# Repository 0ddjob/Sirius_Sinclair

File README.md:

# Сириус (Sirius) Sinclair ZX Spectrum Clone
## Introduction
I have two examples of this machine - they have the same case & keyboard but the motherboard is different.  I'm mainly interested in the smaller board as this seems to be the smallest implementation of a ZX Spectrum I've come across.

This machine was initially a bit of a mystery - well, obviously it's a Sinclair ZX Spectrum clone.  It has all Soviet-era parts (dated mostly 1991 & 1992) including a beautiful, ceramic Т34ВМ1 CPU, a Т34РЕ1-020 ROM (containing the Czechoslovak "Didaktik Skalica" firmware) and absolutely no manufacture markings on the case or motherboard.

Thanks to some sleuthing by Martin (via Patreon) who discovered that the machine (case at least) appears to be a "Sirius" from Russia (confirmed also with UCHC, Ukrainian Computing History Community, on Telegram):
https://sblive.narod.ru/ZX-Spectrum/Sirius/Sirius.htm

Thanks to Eugene on UCHC for his insight:
"Actually, this is one of numerous cheap clones that built around latest Soviet ULA replacement. This one, in particular, created by small garage company with a quite shitty soldering and assembling.  And board itself seems to be assembled somewhere using automated production line, so seems they have ordered boards somewhere else and then assemble them in case. This can explain why boards in these instances are different."

It was initially AC powered with a very simple and unsafe looking transformer (assuming 220VAC-to-9VAC), a КЦ410Б bridge rectifier and a КРЕН5А 5V linear regulator.  I will replace these with a simple 2.1mm DC socket for direct 5VDC input (i.e. USB charger).  On booting it was drawing about 330mA at 5V.

It utilises a Soviet equivalent to a Gate Array or ULA called a БМК (Базового Матричного Кристалла, or Basic Matrix Crystal) ... the КА1515ХМ1-216.  I have had very little success with machines that use this chip actually working ... however it does greatly simplify the circuit design!

The only other major chips are the Т34ВМ1 Soviet Z80 clone, later called the КР1858ВМ1 or КМ1858ВМ1 depending on case type), a Т34РЕ1 (Spectrum ROM), 64KBytes of DRAM using КР565РУ5 and a few other support chips.

The machine only has three ports: 5-pin DIN for joystick, 5-pin DIN for RGBS video & sound output and a 3-pin DIN for cassette input/output.  It also has a reset button.

## Videos
- [Сириус (Sirius) ZX Spectrum Clone: Part 1 (First Look & Power On)](https://youtu.be/TphnZRfjiL4)
- [Сириус (Sirius) ZX Spectrum Clone: Part 2 (RGB & Tape In)](https://youtu.be/R5iWXHqjOgQ)
- [Сириус (Sirius) ZX Spectrum Clone: Part 3 (Smallest Speccy board?)](https://youtu.be/3xgzQrBvwQw)

## [Original Information](/Original_Documentation)
Original schematic & board layout details from [here](https://sblive.narod.ru/ZX-Spectrum/Sirius/Sirius.htm).

## [Updated Schematic](/New_Schematic)
I'm working on creating a cleaner version of the schematic.  I originally wanted to use it as a basis for a new design using the БМК but there is already a modern design available [[LUT216]](https://sblive.narod.ru/ZX-Spectrum/LUT216/LUT216.htm) that looks quite interesting.

### Status
15-Jun-2025: Updated KiCad schematic is work-in-progress<br>

## [Interface Board](/Interface_Board)
Such a beautiful little board deserves to be seen and not hidden away in some ho-hum case.  I'm planning to mount my Sirius board on a Perspex place with a membrane keyboard.  Thus I need a separate board with all the interfaces on it, hence this design.

### Status
15-Jun-2025: Almost completed, finalising design<br>

## [Images](/Images)
Pictures of my machine.

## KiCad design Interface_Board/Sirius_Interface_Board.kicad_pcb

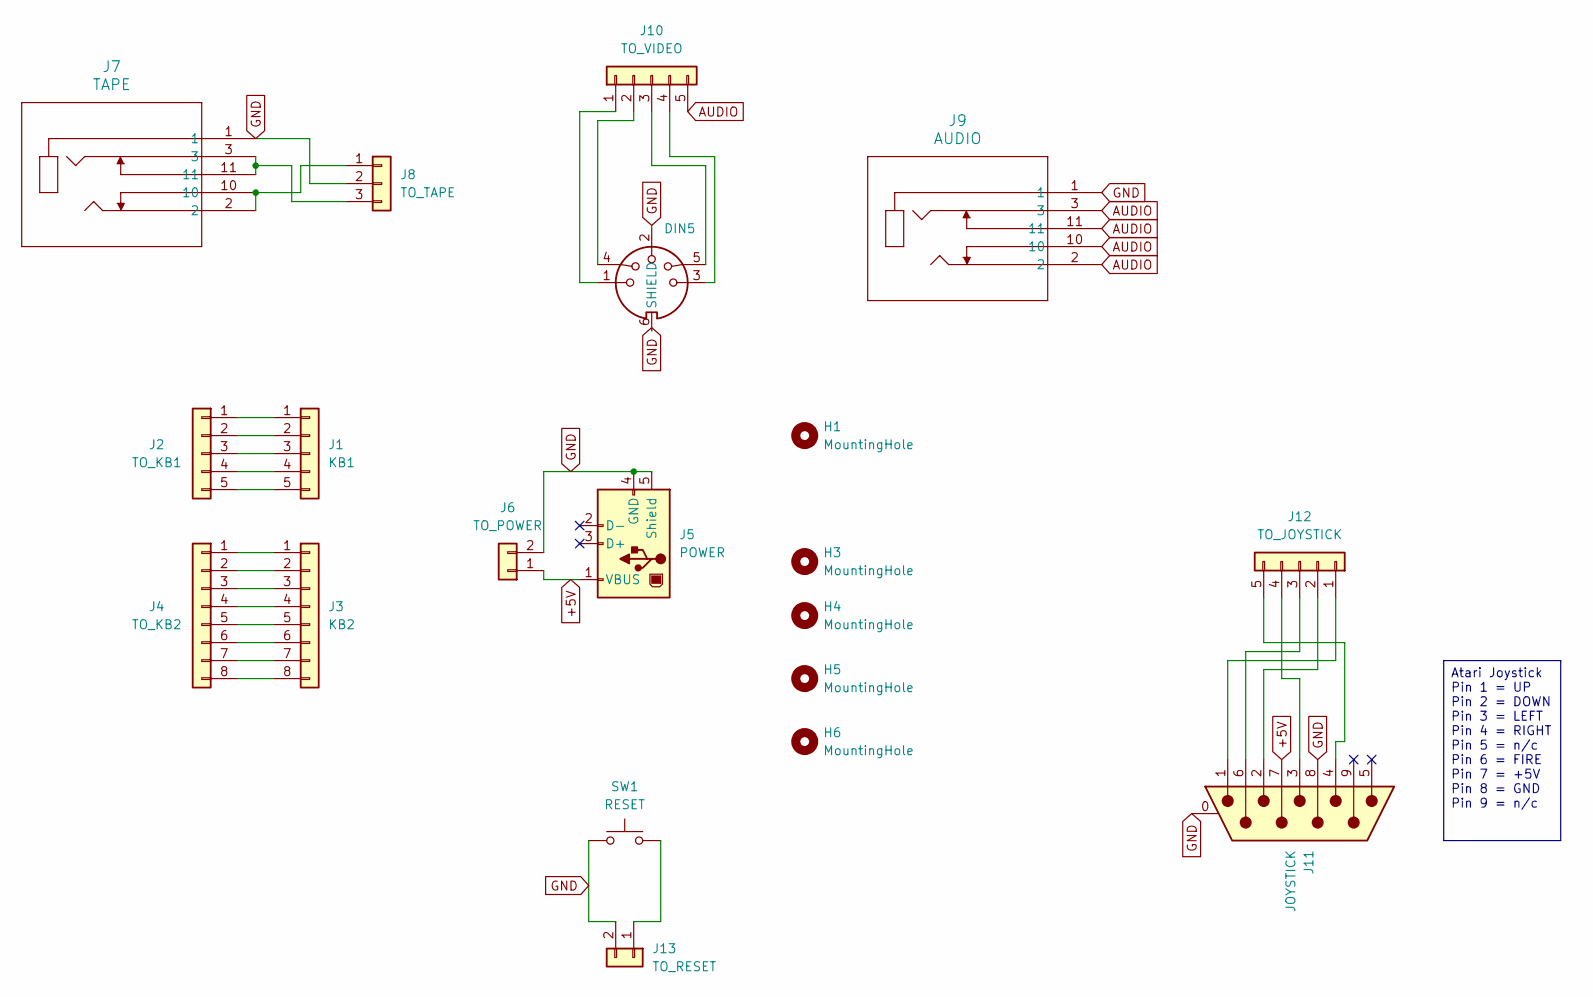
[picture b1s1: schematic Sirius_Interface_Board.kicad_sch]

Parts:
H1, H3, H4, H5, H6: MountingHole; MountingHole_3.2mm_M3
J1: KB1; PinHeader_1x05_P2.54mm_Vertical
J2: TO_KB1; PinHeader_1x05_P2.54mm_Vertical
J3: KB2; PinHeader_1x08_P2.54mm_Vertical
J4: TO_KB2; PinHeader_1x08_P2.54mm_Vertical
J5: POWER; USB_B_Lumberg_2411_02_Horizontal
J6: TO_POWER; PinHeader_1x02_P2.54mm_Vertical
J7: TAPE; 35RAPC4BHN2_SWC
J8: TO_TAPE; PinHeader_1x03_P2.54mm_Vertical
J9: AUDIO; 35RAPC4BHN2_SWC
J10: TO_VIDEO; PinHeader_1x05_P2.54mm_Vertical
J11: JOYSTICK; DSUB-9_Pins_Horizontal_P2.77x2.84mm_EdgePinOffset7.70mm_Hou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
J12: TO_JOYSTICK; PinHeader_1x05_P2.54mm_Vertical
J13: TO_RESET; PinHeader_1x02_P2.54mm_Vertical
J15: DIN5; DIN5_MIDI
SW1: RESET; Switch_Tactile_6mm

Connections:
+5V: J5.1 (VBUS), J6.1, J11.7
AUDIO: J9.2, J9.3, J9.10, J9.11, J10.5
GND: J5.4 (GND), J5.5 (Shield), J6.2, J7.1, J8.2, J9.1, J11.0 (PAD), J11.8, J13.2, J15.2, J15.6 (SHIELD), SW1.1
unnamed: J1.1, J2.1
unnamed: J1.2, J2.2
unnamed: J1.3, J2.3
unnamed: J1.4, J2.4
unnamed: J1.5, J2.5
unnamed: J3.1, J4.1
unnamed: J3.2, J4.2
unnamed: J3.3, J4.3
unnamed: J3.4, J4.4
unnamed: J3.5, J4.5
unnamed: J3.6, J4.6
unnamed: J3.7, J4.7
unnamed: J3.8, J4.8
unnamed: J7.2, J7.10, J8.1
unnamed: J7.3, J7.11, J8.3
unnamed: J10.1, J15.1
unnamed: J10.2, J15.4
unnamed: J10.3, J15.5
unnamed: J10.4, J15.3
unnamed: J11.1, J12.1
unnamed: J11.2, J12.2
unnamed: J11.6, J12.3
unnamed: J11.3, J12.4
unnamed: J11.4, J12.5
unnamed: J13.1, SW1.2

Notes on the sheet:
Atari Joystick Pin 1 = UP Pin 2 = DOWN Pin 3 = LEFT Pin 4 = RIGHT Pin 5 = n/c Pin 6 = FIRE Pin 7 = +5V Pin 8 = GND Pin 9 = n/c

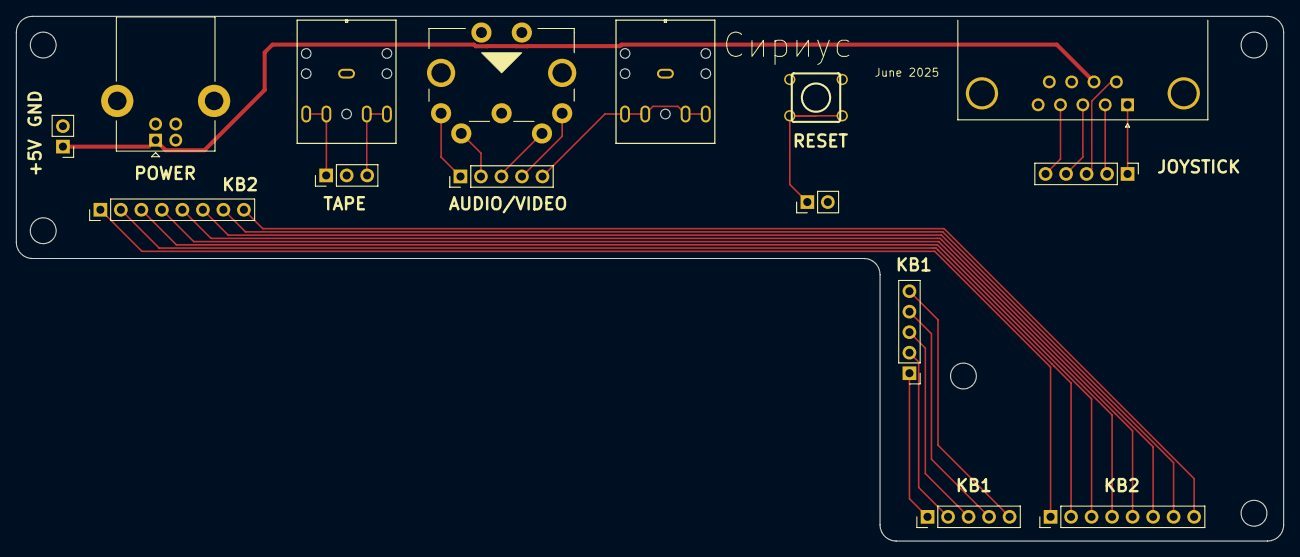
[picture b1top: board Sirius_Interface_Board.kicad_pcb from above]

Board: 2 copper layers, 157.0 x 65.0 mm, 20 parts (0 on the bottom side), 28 nets.

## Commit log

2025-06-15 Cyrillic characters were messed up
2025-06-15 Finalised test PCB design
2025-06-16 Added some text to PCB
